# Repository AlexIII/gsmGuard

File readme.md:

# GsmGuard

A compact multi-purpose all-in-one open source GSM alarm system.
Build on the base of Arduino Pro Mini and Arduino-compatible modules.

## Features
### Communication
The device sends an SMS on any alarm event and optionally a status report once a day.
Why SMS and not internet service? SMS stays most reliable means of mobile communication in cases of poor signal quality, requires less energy and works directly without relying on central server (which needs to be maintained by someone and may present a security  problem).

Example of an alarm SMS:
```
04.11.19 22:37
Movement detected
```
Example of a daily report SMS:
```
door: Closed [04.11.19 09:14] <-- date and time of last door open event
move: None [04.11.19 09:12] <-- date and time of last movement detection event
temp.: 28*C [min. 21*C, max. 28*C, mean 27*C] <-- current temperature and temperature statistics for the current day
light: 99% <-- current illumination level (0 to 100%)
bat.: 4.6v <-- current battery voltage
ext.1: 0 <-- current state of external sensor 1
ext.2: 0 <-- current state of external sensor 2
```

For every alarm event you can also enable a call to your phone or/and sound alarm.

### Sensors

- Door open sensor (magnetic reed switch)
- Illumination level sensor (photoresistor)
- Motion sensor (PIR sensor)
- Temperature sensor (built-in DS3231)

### Alarm events
- Open door
- Rapid illumination change
- Motion detection
- Too high or too low temperature
- Low battery voltage

### Power supply
Three AA batteries. Expected lifetime: 3 to 6 months.

### Configuration and logging
The device can be connected to a PC via USB for configuration.
Configuration program lets you set target phone number, time of daily SMS report, choose events that will be reported, a way of notification (SMS, call, sound alarm) and set time periods during which those events are being monitored. I.e. if you know that the room is being used during some hours in certain days of the week, you can disable the alarm for that period.
It also shows the last 70 events with date and time and a temperature plot for the last 31 days (one measurement every 2 hours).

### Localization

Currently supported languages (SMS and configuration program for PC): English, Russian.

Date format: dd/mm/yy

Temperature units: degrees Celsius

## Assembling guide
### Hardware
#### List of components

List of Arduino modules you will need:

- Arduino Pro Mini 3.3v 8MHz (5v 16MHz is also acceptable, but requires different firmware) 

-  MH-SR602 MINI Motion Sensor 

-  SIM800C GSM Module

-  CP2102 MICRO USB to UART TTL Module

-  DS3231 RTC Module For Raspberry Pi 

Other components

- any >0.5A logic-level P-channel MOSFET in SOT-23

- reed switch

- buzzer 3 to 5v

- electret microphone

- photoresistor

- resistors, capacitors 

The schematics:

#### Important Note
Remove power LED or the resistor that goes in series with it from the Arduino board. Otherwise it will drain the batteries in a matter of few days. It is better to remove voltage regulator IC from the Arduino too, as it's not being used but still draws a little bit of current.
#### Giving out PCBs
I have 9 leftover PCBs of the first iteration that I can send via mail (for free). It's a first version, so it has some errors which you will need to fix with a cutter and a few jump wires. If you interested write me to 

### Software

#### Flashing Arduino

You can upload precompiled `*.hex` firmware to Arduino via [xLoader](http://www.hobbytronics.co.uk/arduino-xloader). There's four firmware files available:

| hex file                       | description                |
| ------------------------------ | -------------------------- |
| gsmGuard-firmware-EN-8MHz.hex  | 8MHz arduino, english SMS  |
| gsmGuard-firmware-EN-16MHz.hex | 16MHz arduino, english SMS |
| gsmGuard-firmware-RU-8MHz.hex  | 8MHz arduino, russian SMS  |
| gsmGuard-firmware-RU-16MHz.hex | 16MHz arduino, russian SMS |

#### Running configuration program

- Windows 

  Run gsmGuardConf_v1.0.exe. It requires no installation, but the unpacking process is rather slow, it may take 10-20 seconds to run.

- Linux

  `~$ python2.7 gsmGuardConf.py`

## Usage notes
- The device pauses its normal operation when it's connected to USB.
- If the device failed to send an SMS, it will try again in 2 minutes, then again in 5, in 10, in 20, twice in 40 and then every 12 hours.
- After a successful call the device will hang-up in 3 minutes.
- The sound alarm will be on for 30 seconds.
- Door, movement and light change events are not monitored for 20 minutes after the last reported event.
- If the device's power was turned off for three hours, the temperature history gets erased.

## Known issues
It looks like PIR sensors perform badly in cold temperature. Mine starts losing stability (frequent false tripping) when ambient temperature drops below +5 Celsius.  I'm sure it havely depends on the particular model, though.

## Project files
- /config-util - PC configuration program. Python 2.7 + Tk + pyserial + matplotlib
- /gsmGuard-firmware - Arduino firmware. In order to successfully compile it, you need to manually install these libs:
  1. RTCLib from https://github.com/NeiroNx/RTCLib (clone the repo or use version ABOVE v1.5.8 if such release exists)
- /kicad-project - KiCAD schematics and board

## License

MIT License © github.com/AlexIII

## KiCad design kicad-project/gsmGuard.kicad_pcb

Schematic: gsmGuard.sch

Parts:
BZ1: Buzzer; Pin_Header_Straight_1x02_Pitch2.54mm
C1, C3, C5, C6: 0.1uF; C_1206
C2: 1000uF 6.3V; CP_Radial_D8.0mm_P3.50mm
C4: 33uF 6.3V; CP_Tantalum_Case-C_EIA-6032-28_Reflow
D1, D2, D3, D4: MBR0520LT; D_SOD-123F
D5: 1N4148W; D_SOD-123F
J1: Conn_01x02_Female; Pin_Header_Straight_1x02_Pitch2.54mm
J2: Conn_01x03_Male; PhoenixContact_MC-G_03x3.81mm_Angled
J3: Conn_01x04_Male; PhoenixContact_MC-G_04x3.81mm_Angled
MK1: Microphone; Pin_Header_Straight_1x02_Pitch2.54mm
Q1: IRLML6401; SOT-23
R1: 1-300k; Resistor_LDR_4.9x4.2_RM2.54
R2, R3, R4, R5, R9, R12, R13, R14: 4.7k; R_1206
R6, R8: 1M; R_1206
R7: 300k; R_1206
R10, R11: 1k; R_1206
SW1: SW_Reed; reed-1
U1: ArduinoProMini; pro_mini
U2: RTC_DS3231; Pin_Header_Straight_1x05_Pitch2.54mm
U3: USB_UART; Pin_Header_Straight_1x06_Pitch2.54mm
U4: SIM800C
U5: MH-SR602; Pin_Header_Straight_1x03_Pitch2.54mm

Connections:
A0: C6.1, R1.2, R2.1, U1.17 (A0)
A1: C1.1, R6.2, R7.1, U1.18 (A1)
D5: Q1.1, R9.2, U1.8 (D5)
D6: C5.1, R14.1, U1.9 (D6)
D7: C3.1, R8.2, SW1.2, U1.10 (D7)
D8: BZ1.1, U1.11 (D8)
D9: J2.2, R5.2, U1.12 (D9)
D10: J3.2, U1.13 (D10)
D11: J3.3, U1.14 (MOSI/D11)
D12: R13.2, U1.15 (MISO/D12)
GND: BZ1.2, C1.2, C2.2, C3.2, C4.2, C5.2, C6.2, J1.2, J2.3, J3.4, R2.2, R7.2, R11.1, R12.1, SW1.1, U1.4 (GND), U2.5 (GND), U3.5 (GND), U4.6 (GND), U5.1 (GND)
M_ON: U1.5 (D2), U4.3 (BOOT)
unnamed: D1.1, U1.31 (TX)
unnamed: D1.2, R10.2, U3.3 (RX)
unnamed: D2.1, R11.2, U1.32 (RX)
unnamed: D2.2, U3.4 (TX)
unnamed: D3.2, R10.1, R12.2, R13.1, U3.6 (5.0V)
unnamed: D4.2, J1.1, Q1.2, R9.1
unnamed: D5.1, U4.2 (VCC)
unnamed: MK1.1, U4.10 (MICP)
unnamed: MK1.2, U4.9 (MICN)
unnamed: R14.2, U5.3 (OUT)
unnamed: U1.30 (DTR), U3.2 (DTR)
RX: U1.6 (D3), U4.4 (RXD)
SCL: R4.2, U1.26 (SCL/A5), U2.3 (SCL)
SDA: R3.2, U1.25 (SDA/A4), U2.2 (SDA)
TX: U1.7 (D4), U4.5 (TXD)
VBAT: C4.1, D3.1, D4.1, R6.1, R8.1, U1.21 (VCC), U5.2 (VCC)
VMOD: C2.1, D5.2, Q1.3
VSENS: J2.1, J3.1, R1.1, R3.1, R4.1, R5.1, U1.16 (SCK/D13), U2.1 (VCC)

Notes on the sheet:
to battery 4.5v
1-wire
ext. sens
github.com/AlexIII/GsmGuard

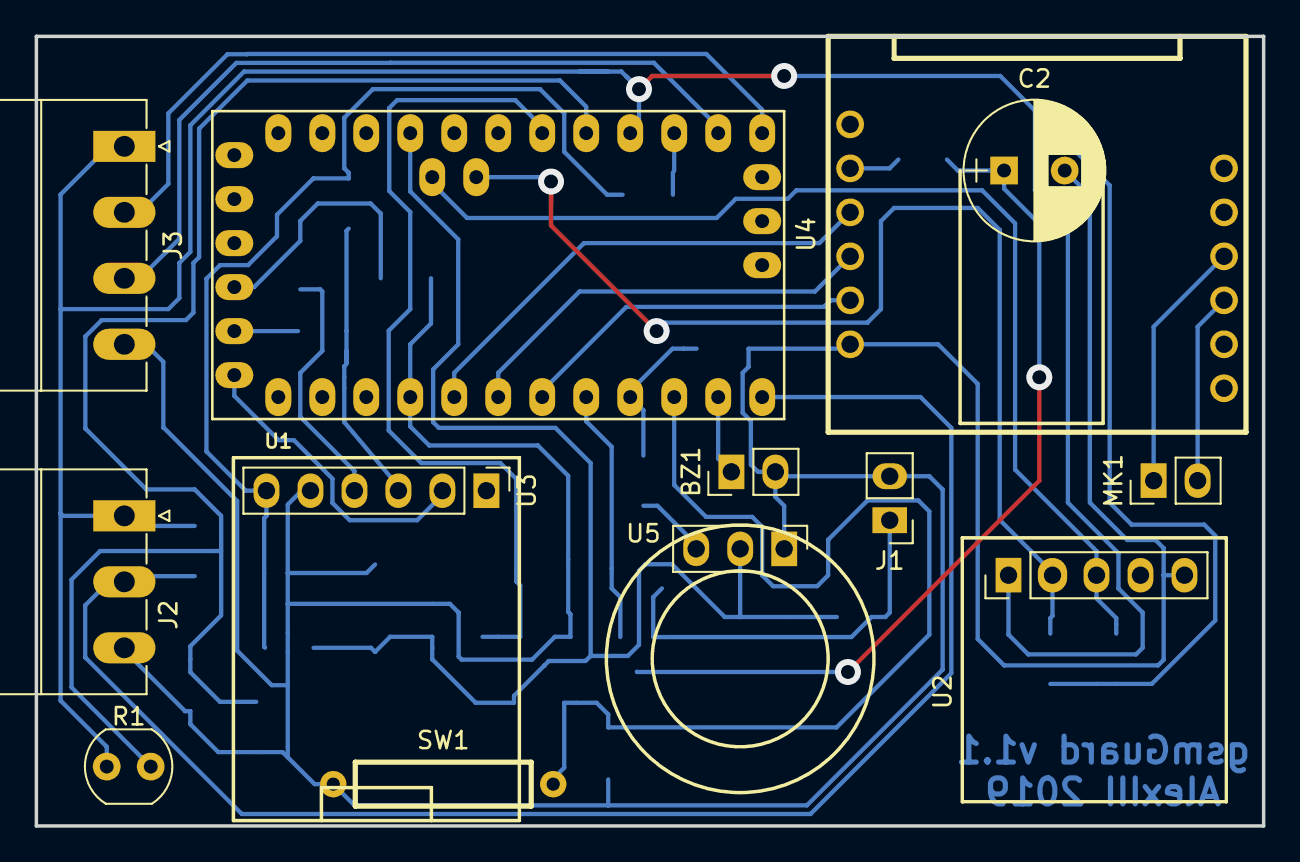
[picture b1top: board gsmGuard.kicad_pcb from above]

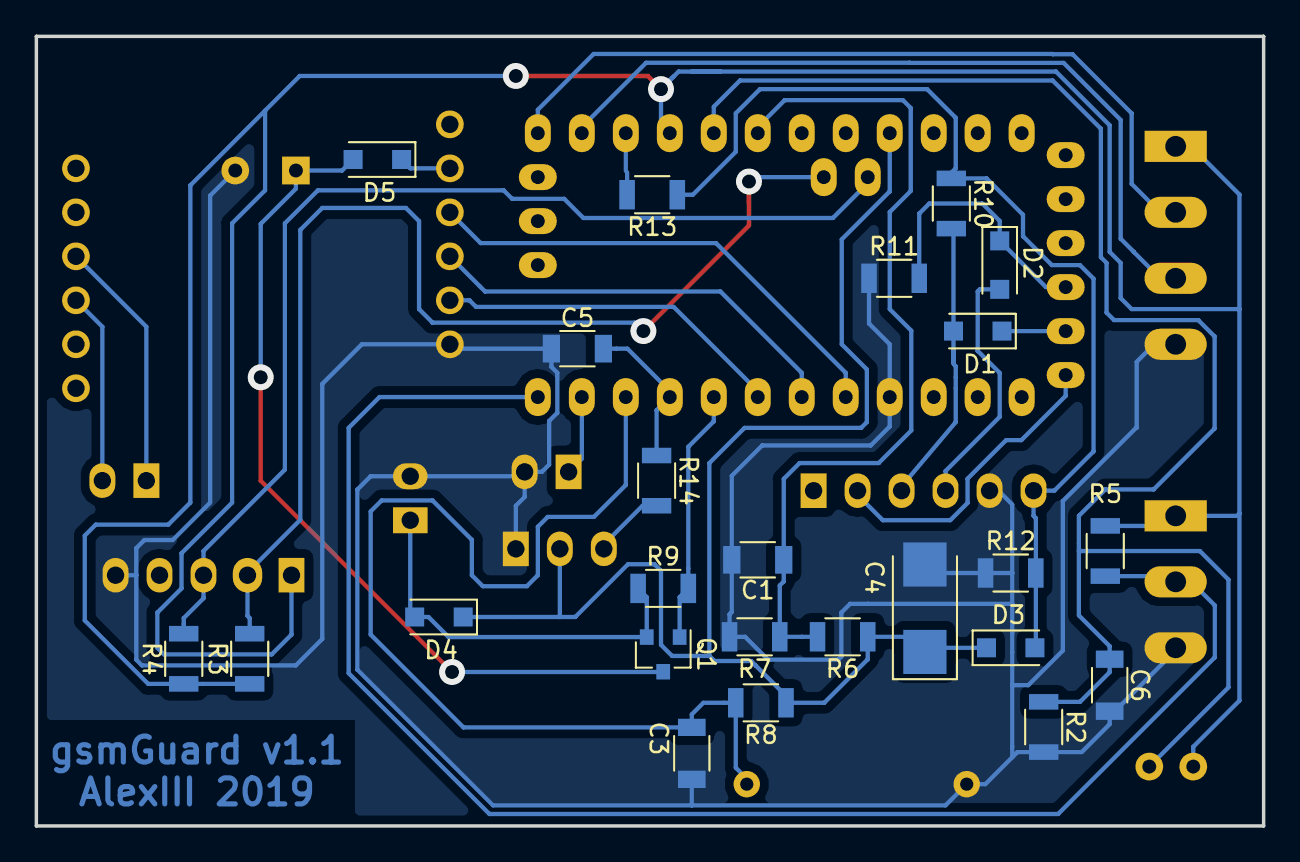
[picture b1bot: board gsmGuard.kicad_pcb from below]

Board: 2 copper layers, 70.9 x 45.6 mm, 37 parts (24 on the bottom side), 30 nets.

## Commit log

2019-12-15 fix readme
2019-12-19 add 'Known issues' to readme
2019-12-21 improve PIR sensor stability
2019-12-21 fix resistor values
2019-12-21 use EEvar library, fix 16MHz boards support
2019-12-21 remove 2 of 4 hacks of Arduino IDE needed for compilation
2019-12-22 fix readme: no Arduino IDE tweaks are needed
2019-12-28 small renaming
2019-12-28 add setting 'Max one report in 20min'
2020-01-02 config: enable/disable temperature alarm
2020-04-02 allow phone number from 5 to 12 digits
2020-04-02 update arduino libs
2020-04-02 forgot to update version...
2020-04-03 config util bugfix, fix readme
2020-04-05 firmware stack owerflow fix
